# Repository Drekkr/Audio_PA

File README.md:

# Audio_PA_AMP

Intended Power supply: +/- 45V;
Intended Power: 100W;
Intended input: 1,2V;

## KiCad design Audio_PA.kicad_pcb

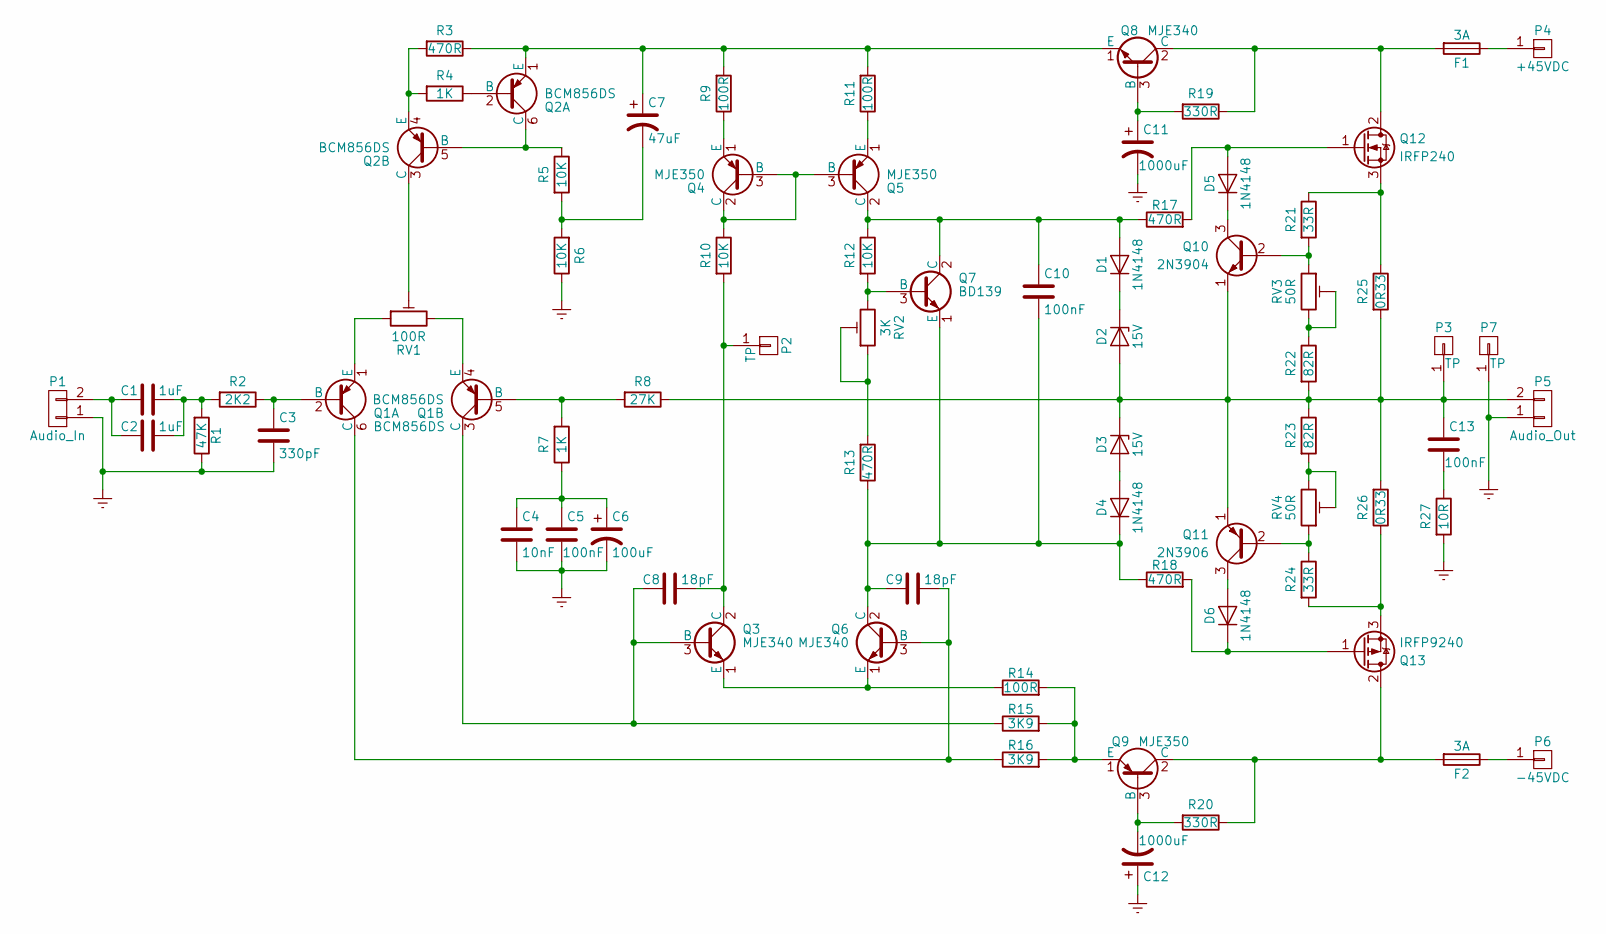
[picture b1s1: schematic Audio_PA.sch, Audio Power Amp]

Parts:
C1, C2: 1uF; C_Rect_L27_W9_H17_P23
C3: 330pF; C_Rect_L7_W4.5_P5
C4: 10nF; C_Rect_L7_W2.5_P5
C5, C10, C13: 100nF; C_Rect_L7_W2.5_P5
C6: 100uF; C_Radial_D13_L21_P5; Voltage >=50V
C7: 47uF; C_Radial_D10_L16_P5
C8, C9: 18pF; C_Rect_L4_W2.5_P2.5
C11, C12: 1000uF; C_Radial_D16_L31.5_P7.5
D1, D4, D5, D6: 1N4148; Diode_DO-35_SOD27_Horizontal_RM10
D2, D3: 15V; Diode_DO-41_SOD81_Horizontal_RM10
F1, F2: 3A; Fuseholder5x20_horiz_SemiClosed_Casing10x25mm
P1: Audio_In; PhoenixContact_MCV-G_02x3.81mm_Vertical
P2, P3, P7: TP; 1pin
P4: +45VDC; 1pin
P5: Audio_Out; PhoenixContact_MCV-G_02x3.81mm_Vertical
P6: -45VDC; 1pin
Q1, Q2: BCM856DS; TSOT-6-MK06A_Handsoldering
Q3, Q6, Q8: MJE340; SOT126_SOT32_Housing_Vertical
Q4, Q5, Q9: MJE350; SOT126_SOT32_Housing_Vertical
Q7: BD139; SOT126_SOT32_Housing_Vertical
Q10: 2N3904; TO-92_Inline_Narrow_Oval
Q11: 2N3906; TO-92_Inline_Narrow_Oval
Q12: IRFP240; TO-247_Vertical_Neutral123
Q13: IRFP9240; TO-247_Vertical_Neutral123
R1: 47K; Resistor_Horizontal_RM10mm
R2: 2K2; Resistor_Horizontal_RM10mm
R3, R13, R17, R18: 470R; Resistor_Horizontal_RM10mm
R4, R7: 1K; Resistor_Horizontal_RM10mm
R5, R6, R10, R12: 10K; Resistor_Horizontal_RM10mm
R8: 27K; Resistor_Horizontal_RM10mm
R9, R11, R14: 100R; Resistor_Horizontal_RM10mm
R15, R16: 3K9; Resistor_Horizontal_RM10mm
R19, R20: 330R; Resistor_Horizontal_RM10mm
R21, R24: 33R; Resistor_Horizontal_RM10mm
R22, R23: 82R; Resistor_Horizontal_RM10mm
R25, R26: 0R33; Resistor_Ceramic_Horizontal_L50mm-W14mm-H13mm-p60mm
R27: 10R; Resistor_Ceramic_Horizontal_L19mm-W8mm-H8mm-p25mm
RV1: 100R; Potentiometer_Bourns_3296Y_3-8Zoll_Angular_ScrewUp
RV2: 3K; Potentiometer_Bourns_3296Y_3-8Zoll_Angular_ScrewUp
RV3, RV4: 50R; Potentiometer_Bourns_3296Y_3-8Zoll_Angular_ScrewUp

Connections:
Earth: C3.2, C4.2, C5.2, C6.2, C11.2, C12.1, P1.1, P5.1, P7.1, R1.1, R6.1, R27.2
unnamed: C1.1, C2.1, P1.2
unnamed: C1.2, C2.2, R1.2, R2.2
unnamed: C3.1, Q1.2 (B), R2.1
unnamed: C4.1, C5.1, C6.1, R7.1
unnamed: C7.1, Q2.1 (E), Q8.1 (E), R3.1, R9.2, R11.2
unnamed: C7.2, R5.2, R6.2
unnamed: C8.1, Q1.3 (C), Q3.3 (B), R15.1
unnamed: C8.2, P2.1, Q3.2 (C), R10.2
unnamed: C9.2, Q1.6 (C), Q6.3 (B), R16.1
unnamed: C10.1, D1.2 (A), Q5.2 (C), Q7.2 (C), R12.1, R17.1
unnamed: C9.1, C10.2, D4.1 (K), Q6.2 (C), Q7.1 (E), R13.1, R18.1
unnamed: C11.1, Q8.3 (B), R19.2
unnamed: C12.2, Q9.3 (B), R20.2
unnamed: C13.1, D2.2 (A), D3.1 (K), P3.1, P5.2, Q10.1 (E), Q11.1 (E), R8.1, R22.2, R23.1, R25.2, R26.2
unnamed: C13.2, R27.1
unnamed: D1.1 (K), D2.1 (K)
unnamed: D3.2 (A), D4.2 (A)
unnamed: D5.1 (K), Q10.3 (C)
unnamed: D5.2 (A), Q12.1 (G), R17.2
unnamed: D6.1 (K), Q13.1 (G), R18.2
unnamed: D6.2 (A), Q11.3 (C)
unnamed: F1.1, P4.1
unnamed: F1.2, Q8.2 (C), Q12.2 (D), R19.1
unnamed: F2.1, P6.1
unnamed: F2.2, Q9.2 (C), Q13.2 (D), R20.1
unnamed: Q1.1 (E), RV1.1
unnamed: Q1.4 (E), RV1.3
unnamed: Q1.5 (B), R7.2, R8.2
unnamed: Q2.2 (B), R4.1
unnamed: Q2.3 (C), RV1.2
unnamed: Q2.4 (E), R3.2, R4.2
unnamed: Q2.5 (B), Q2.6 (C), R5.1
unnamed: Q3.1 (E), Q6.1 (E), R14.1
unnamed: Q4.1 (E), R9.1
unnamed: Q4.2 (C), Q4.3 (B), Q5.3 (B), R10.1
unnamed: Q5.1 (E), R11.1
unnamed: Q7.3 (B), R12.2, RV2.3
unnamed: Q9.1 (E), R14.2, R15.2, R16.2
unnamed: Q10.2 (B), R21.2, RV3.1
unnamed: Q11.2 (B), R24.1, RV4.1
unnamed: Q12.3 (S), R21.1, R25.1
unnamed: Q13.3 (S), R24.2, R26.1
unnamed: R13.2, RV2.1, RV2.2
unnamed: R22.1, RV3.2, RV3.3
unnamed: R23.2, RV4.2, RV4.3

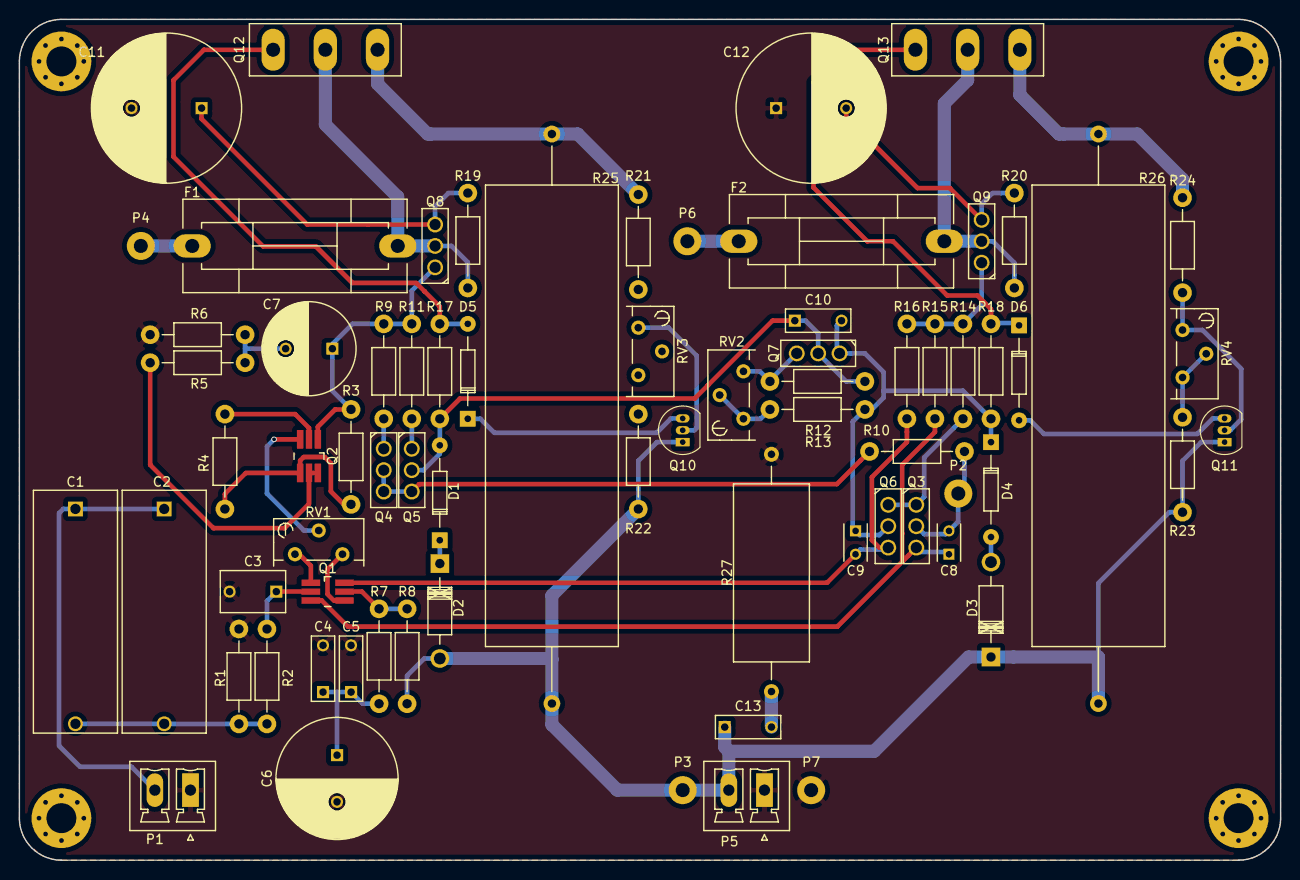
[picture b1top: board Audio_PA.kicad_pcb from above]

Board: 2 copper layers, 135.0 x 90.0 mm, 72 parts (0 on the bottom side), 46 nets.

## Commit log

2017-01-08 Initial README info added
2017-01-08 KiCAD Project Created
2017-01-08 AMP Schematic library added
2017-01-08 Electric circuit Ver_1
2017-01-09 Electric circuit Ver_1.1
2017-01-09 Electric circuit Ver_1.2
2017-01-09 Footprints Added
2017-01-11 Electric circuit Ver_1.3
2017-01-12 Layout V1 added
2017-01-18 Layout V1.1 + routing V1
2017-01-19 Routing done
